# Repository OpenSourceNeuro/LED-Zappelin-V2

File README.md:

<h1 align="center"> LED Zappelin' v2</h1>
<h3 align="center">  An Open Source and versatile LED controller for arbitrary spectrum visual stimulation and optogenetics during two-photon imaging.</h3></p>
<h6 align="right">developed by M.J.Y. Zimmermann, A.M. Chagas & T. Baden</h6>

<br>

This project is licensed under the <a href="https://www.gnu.org/licenses/gpl-3.0.html">GNU General Public License v3.0</a>
<br>
The hardware is licensed under the <a href="https://cern-ohl.web.cern.ch">CERN OHL v1.2</a>

***

<p style='text-align: justify;'>
Two-photon microscopy is a cornerstone technique in neuroscience research, but combining this technology with spectrally arbitrary light stimulation can be challenging due to crosstalk between stimulation light and fluorescence detection. To overcome this limitation, we present LED Zappelin': a simple and low-cost electronic solution to rapidly time-interleave stimulation and detection epochs during scans.
</p>

The second version of this project allows user to either:

  - Independently drive up to 24 arbitrary spectrum LEDs to meet user requirements. Using the <a href="https://www.ti.com/lit/ds/symlink/tlc5947.pdf">TLC5947 LED driver</a>.
  - Control external light source generator such as the <a href="https://www.thorlabs.com/newgrouppage9.cfm?objectgroup_id=13597">Thorlabs Chrolis</a>. Using TTL logic circuits.

</br>

<h5 align="justify"> <em>Left: </em>LED Zappelin' mounted with a TLC 5947 controlling up to 24 LED channels. <em>Right: </em>LED Zappelin' mounted with TTL circuit controlling two 6-High_Power LED Chrolis systems</h5>

<br></br>

<p style='text-align: justify;'>
In the <a href=https://pubmed.ncbi.nlm.nih.gov/35498254/>original publication</a>, we demonstrate the utility of our stimulator for colour vision experiments on the in vivo tetra-chromatic zebrafish retina and for optogenetic circuit mapping in Drosophila.
</p>

<br>

- [Introduction](#Introduction)
- [BoM](https://github.com/BadenLab/LED-Zappelin/blob/master/Bills%20of%20Materials/BOM%20-%20Stimulator.csv)
- [Request a Quote]()
- [A stimulator for visual neuroscience](#Colour-Vision-Experiment)
- [A stimulator for optogenetics](#Optogenetics-Experiment)
- [A detailed assembly and instruction manual](https://github.com/BadenLab/LED-Zappelin/blob/master/Instruction%20Manual/README.md)
- [A step by step calibration script](https://github.com/BadenLab/LED-Zappelin/blob/master/Instruction%20Manual/Stimulator%20Calibration/Stimulator_Calibration.ipynb)
- [Repository Structure](#Repository-Structure)

<br>

## Introduction

<p align="justify">
Combining two-photon imaging with additional light stimulation – for example for visual stimulation or for driving optogenetic actuators – has remained challenging because the stimulation light can interfere with fluorescence detection. This can result in light artefacts in the image and/or may damage sensitive fluorescence detection equipment (e.g. photomultiplier tubes, PMTs).
</p>

<p align="justify">

A temporal separation between light stimulation and fluorescence detection, for example during the scan-retrace, can ameliorate these problems.
This problem can be readily solved electronically, for example through use of a microcontroller.
</p>

<br>

<p align="justify">
Here, we present such a solution. Our system can either line-synch up to 24 independent LED channels or can be connected to external commercial light sources, and can be assembled from off-the-shelf components for substantially below $200. This provides for flexible options of spectrally diverse light stimulation during two-photon scanning and comfortably provides sufficient power to drive standard optogenetics actuators such as CsChrimson.
</p>

<br>

<p align="justify">
Alongside, we also provided <a href="https://github.com/OpenSourceNeuro/LED-Zappelin-V2/tree/main/Casing%20Files">custom casing files</a> (for either 3d print or laser-cut), <a href="https://github.com/OpenSourceNeuro/LED-Zappelin-V2/tree/main/3D%20files">designed suggestions</a> for optically combining LED banks using Thorlabs parts, and an alternative 3D-printed LED holder and microscope chamber.
</p>

<p align="justify">
The device is built around an <a href="https://www.espressif.com/en/products/socs/esp32">ESP32</a>, a microcontroller which exchange signals with the recording setup, drive the light sources and runs on C++. However, users do not need to interfere with the source code as we provide an intuitive and interactive <a href="">Graphical User Interface</a> (GUI), from which all functions and variables can be manipulated.
</p>

</br>

<h5 align="justify"> <em>Left: </em>LED Zappelin' GUI controlling 4 LEDs, all executing a chirp stimulus. <em>Right: </em>LED Zappelin' controlling 12 LED channels from two Chrolis systems, executing successive On/Off stimulati</h5>

<br></br>

<p align="justify">
<a href="https://github.com/OpenSourceNeuro/LED-Zappelin-V2/blob/main/GUI_UserManual.md"><strong>Here</strong></a>, is the full user guide documentation.
</p>

<br>

***

## Colour Vision Experiment

<p align="justify">
We used LED Zappelin' for studying the retinal processing of the tetra-chromatic zebrafish retina in response to multichromatic signal.
Here we selected four LEDs that match the peak sensitivities of each cone opsins of our model.
We chose LEDs and band pass filters in such manner that the stimulating light and the detection bands do not overlap as much as possible. However a temporal separation is still necessary to avoid some overlapping and any light artefact.
</p>

</br>

<h5 align="justify"> <em>Left: </em>Zebrafish's opsin absorbance spectra overlapped with four filtered LED spectra. <em>Right: </em>The four selected stimulation LEDs along the microscope setup spectra features</h5>

<br></br>

<p align="justify">
 We recorded light-driven calcium signals under 2-photon from <a href="https://pubmed.ncbi.nlm.nih.gov/29937350/"> retinal bipolar cells in vivo in the tetra-chromatic larval zebrafish</a>. We used a transgenic line expressing a genetically encoded biosensors for calcium at the  bipolar cell synaptic terminals level (ctbp2:SyGCaMP6)  within the inner plexiform layer (IPL).
</p>

<p align="justify">
Following <a href="https://pubmed.ncbi.nlm.nih.gov/2321027/">established protocols</a>, we used a Sutter MOM microscope where light stimulation is displayed through the objective directly onto the fish retina along with the laser excitation. Fluorescence is also collected through the objective as well as from below the stage (not shown).
</p>

<p align="justify">
We presented full field steps of red, green, blue and UV light to the fish eye (respectively 567, 480, 420 and 365nm), and recorded evoked calcium signals as a readout of synaptic activity. We observed spectrally different tunings from distinct bipolar cell terminals  without detectable stimulus artefact across the scan.
</p>

<h5 align="justify"> a) Overview of the setup described for the visual stimulation experiment performed on the tetra-chromatic zebrafish. b) Drawing of the larval zebrafish retina highlighting the IPL. c) 2 photon scan field of the IPL with regions-of-interest marked by red circles. The 64x32 pixel image was obtained by at 1ms scan rate. d) Ca²⁺ traces (mean traces in black, n=5 trials in grey) in response to consecutive red, green, blue and UV On/Off flashes. e) Trigger timing recorded by the DAQ highlighting its accuracy over time with a precision of 0.1µs. t(n+1) = t(n) + T, where “t” is the recorded trigger time and “T” the trigger period. </5>

***

## Optogenetics Experiment

In addition to colour vision experiments, LED Zappelin' is well suited for optogenetic manipulations.

<p align="justify">
Here we illustrate this application in Drosophila larvae, were we recorded brain-wide calcium signals under 2P in response to optogenetic stimulation of all olfactory sensory neurons (OSNs).  We expressed the red-shifted channel rhodopsin CsChrimson OSNs and the genetically encoded calcium indicator GCaMP6s pan-neuronally by using larvae with the genotype: elav-Gal4;UAS-GCaMP6s/Orco-LexA;LexAOp-CsChrimson.
</p>

<p align="justify">
We placed first instar larvae under a custom-made 2P microscope in a <a href"https://github.com/OpenSourceNeuro/LED-Zappelin-V2/tree/main/3D%20files/Optogenetics%20Components">3D-printed optogenetics LED chamber</a>.
Red light stimulation was delivered from around the sides of the recording chamber and GCaMP6s fluorescence intensity was collected by two detectors one through the objective lens, and a sub-stage PMT.
We presented full field illumination steps of 615 nm light lasting 0.5 s and an inter-stimulus interval of either 3 s (b) or 10 s (c).
</p>

<p align="justify">
We observed robust stimulus-evoked activity in the primary olfactory sensory centres of the larval brain, the antennal lobes (red outlines). Similarly to colour vision experiments, we detected no light artefact.
</p>

<h5 align="justify">  a) Schematic of a fruit fly first instar larval head expressing the red-shifted channel rhodopsin CsChrimson in olfactory sensory neurons and GCaMP6s in all neurons. b) Rendering of the experimental setup: The mounting chamber is placed in a 3D-printed holder, screwed onto a rigid stand (ThorLabs).  c),d)  2 photon scan field of the larval brain with antennal lobes marked by red circles (left) and Ca²⁺ traces in response to red flashes (right). c. Stimulation duration = 0.5 s, inter-stimulus interval = 3 s, image dimensions = 256 x 230, scan rate = 1081 Hz, frame rate = 4.7 Hz. d) Stimulation duration = 0.5 s, inter-stimulus interval = 10 s, image dimensions = 256 x 170, scan rate = 1077Hz, frame rate = 6.34 Hz. </h5>

***
## Repository structure (to be updated)

```
├───3D Designs                                Contains printed parts for the stimulator and optical components
│   ├───Optical Components
|   |   ├───STL renderings                    - Printing files
|   |   └───SCAD files                        - SCAD files to be modified if need be
│   ├───Optogenetics Components
|   |   ├───STL renderings                    - Printing files
|   |   └───SCAD files                        - SCAD files to be modified if need be
│   └───Stimulator
|       ├───STL renderings                    - Printing files
|       └───SCAD files                        - SCAD files to be modified if need be
|
├───Arduino Code                              Stimulator Code
|   ├───Stimulator Code                       - Adaptable C+ code for running the stimulator
|   └───LED driver library                     - Library to run the TLC 5947
|
├───Bill of Materials                         List of necessary components and retailer suggestions
|
├───Datasheets                                - Contains all technical sheet for:
|   ├───Optical Components                    - ...LEDs, Filters, Dichroic Mirrors used in the presented example
|   ├───Stimulator                            - ...micro-controller and LED driver
|   └───Spectrometer                          - ...device used for calibration
|
├───Images                                    Image repository
|
├───Instruction Manual                        Detailed manual to assemble and calibrate the stimulator
|   └───Stimulator Calibration                - Contains calibration recordings and the adaptable jupyter notebook script to calibrate the stimulator
|       ├───Arduino Calibration Code          - Sequence used for the calibration
|       ├───Calibration Figures               - Illustration from calibration measurements
|       ├───Filters                           - Filters and dicroic mirrors spectra
|       ├───Powermeter Recording              - Recording of the calibration sequence
|       ├───Spectrometer Recording            - Recording of the calibration sequence
|       └───Stimulator Calibration            - iPython Jupyter Notebook script for calibration
|
├───PCB                                       KiCad and Gerber files to modified and generate PCB for:
│   ├───Potentiometer mounts                  - ...trimmer potentiometers that set the LED maximum brightness
│   └───Stimulator                            - ...the stimulator itself
|
└───References                                Publication used to design and conceive this model

```

***

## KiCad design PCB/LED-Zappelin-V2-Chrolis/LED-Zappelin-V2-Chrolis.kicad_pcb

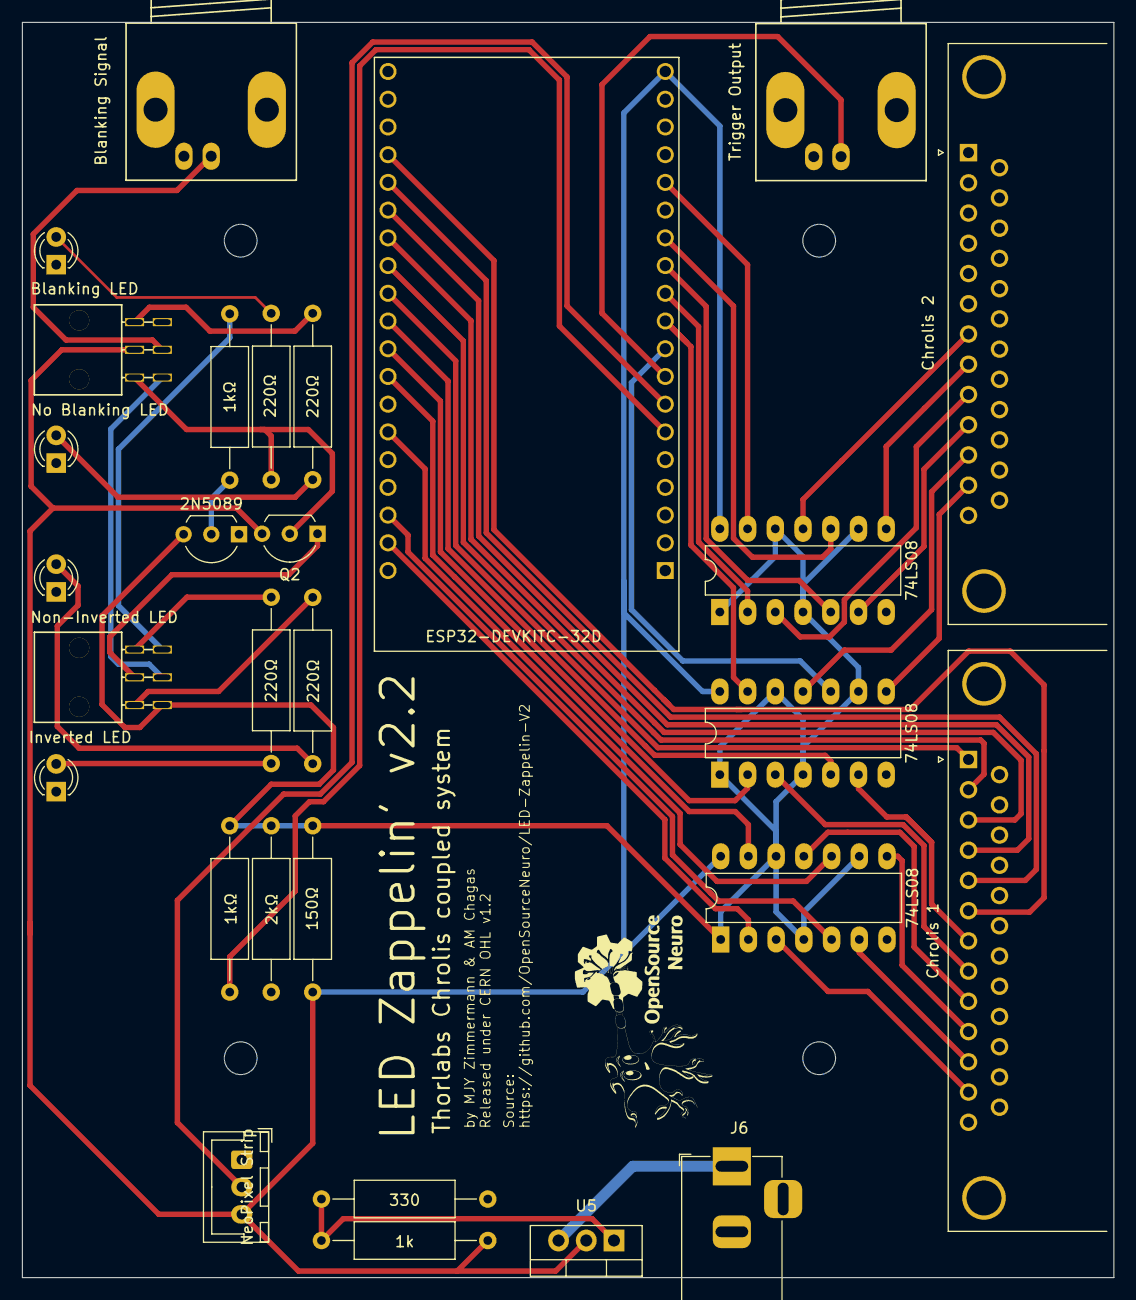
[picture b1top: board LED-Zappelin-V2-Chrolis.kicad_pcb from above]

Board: 2 copper layers, 100.0 x 115.0 mm, 33 parts (0 on the bottom side), 51 nets.

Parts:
D1: Blanking LED; LED_D3.0mm
D2: No Blanking LED; LED_D3.0mm
D3: Inverted LED; LED_D3.0mm
D4: Non-Inverted LED; LED_D3.0mm
H1, H2, H3, H4: MountingHole; MountingHole_3mm
J1: Blanking Signal; BNC_Socket_TYCO-AMP_LargePads
J2: Trigger Output; BNC_Socket_TYCO-AMP_LargePads
J3: Chrolis 1; DSUB-25_Female_Horizontal_P2.77x2.84mm_EdgePinOffset9.90mm_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
J4: Chrolis 2; DSUB-25_Female_Horizontal_P2.77x2.84mm_EdgePinOffset9.90mm_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
J5: NeoPixel Strip; JST_XH_B3B-XH-A_1x03_P2.50mm_Vertical
J6: Barrel_Jack; BarrelJack_Horizontal
Q1, Q2: 2N5089; TO-92L_Inline_Wide
R1, R6: 1kΩ; R_Axial_DIN0309_L9.0mm_D3.2mm_P15.24mm_Horizontal
R2: 2kΩ; R_Axial_DIN0309_L9.0mm_D3.2mm_P15.24mm_Horizontal
R3, R4, R7, R8: 220Ω; R_Axial_DIN0309_L9.0mm_D3.2mm_P15.24mm_Horizontal
R5: 150Ω; R_Axial_DIN0309_L9.0mm_D3.2mm_P15.24mm_Horizontal
R9: 1k; R_Axial_DIN0309_L9.0mm_D3.2mm_P15.24mm_Horizontal
R10: 330; R_Axial_DIN0309_L9.0mm_D3.2mm_P15.24mm_Horizontal
SW1: Blanking Switch; maxi_DPDT_Angled
SW2: Blanking Inverter Switch; maxi_DPDT_Angled
U1: ESP32-DEVKITC-32D; MODULE_ESP32-DEVKITC-32D
U2, U3, U4: 74LS08; DIP-14_W7.62mm_LongPads
U5: LM317_TO-220; TO-220-3_Vertical

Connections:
5V: J5.3, Q2.3 (C), R5.2, R9.2, SW1.5 (B), U1.19 (EXT_5V), U2.14 (VCC), U3.14 (VCC), U4.14 (VCC), U5.2 (VO)
+9V: J6.1, U5.3 (VI)
Blanking: Q1.3 (C), R1.2, R2.2, R5.1, SW2.3 (C), U2.1, U2.4, U2.9, U2.12, U3.1, U3.4, U3.9, U3.12, U4.1, U4.4, U4.9, U4.12
GNDREF: D1.1 (K), D2.1 (K), D3.1 (K), D4.1 (K), J1.2 (Ext), J2.2 (Ext), J3.13, J3.14, J3.15, J3.16, J3.17, J3.18, J3.19, J3.20, J3.21, J3.22, J3.23, J3.24, J3.25, J4.13, J4.14, J4.15, J4.16, J4.17, J4.18, J4.19, J4.20, J4.21, J4.22, J4.23, J4.24, J4.25, J5.1, J6.2, Q1.1 (E), R2.1, R10.1, U1.14 (GND1), U1.20 (GND3), U1.26 (GND2), U2.7 (GND), U3.7 (GND), U4.7 (GND)
GPIO00: J3.4, U1.33 (IO0)
GPIO02: J3.5, U1.34 (IO2)
GPIO04: J3.3, U1.32 (IO4)
GPIO05: U1.29 (IO5), U3.5
GPIO12: U1.13 (IO12), U4.10
GPIO13: U1.15 (IO13), U4.13
GPIO15: J3.6, U1.35 (IO15)
GPIO16: J3.2, U1.31 (IO16)
GPIO17: J3.1, U1.30 (IO17)
GPIO18: U1.28 (IO18), U3.2
GPIO19: U1.27 (IO19), U2.13
GPIO21: U1.25 (IO21), U2.10
GPIO22: U1.22 (IO22), U2.5
GPIO23: U1.21 (IO23), U2.2
GPIO25: U1.9 (IO25), U3.10
GPIO26: U1.10 (IO26), U3.13
GPIO27: U1.11 (IO27), U4.2
GPIO28: U1.12 (IO14), U4.5
GPIO Input 1: J3.12, U2.3
GPIO Input 2: J3.11, U2.6
GPIO Input 3: J3.10, U2.8
GPIO Input 4: J3.9, U2.11
GPIO Input 5: J3.8, U3.3
GPIO Input 6: J3.7, U3.6
GPIO Input 7: J4.12, U3.8
GPIO Input 8: J4.11, U3.11
GPIO Input 9: J4.10, U4.6
GPIO Input 10: J4.9, U4.3
GPIO Input 11: J4.8, U4.8
GPIO Input 12: J4.7, U4.11
NeoPixel: J5.2, U1.7 (IO32)
unnamed: D1.2 (A), R3.1
unnamed: D2.2 (A), R4.1
unnamed: D3.2 (A), R7.1
unnamed: D4.2 (A), R8.1
unnamed: J1.1 (In), SW1.2 (B)
unnamed: Q1.2 (B), R6.1
unnamed: Q2.2 (B), R3.2, SW1.6 (C)
unnamed: Q2.1 (E), SW2.5 (B)
unnamed: R4.2, SW1.4 (A)
unnamed: R6.2, SW2.1 (A)
unnamed: R7.2, SW2.4 (A)
unnamed: R8.2, SW2.6 (C)
unnamed: SW1.3 (C), SW2.2 (B)
unnamed: R1.1, U1.6 (IO35)
unnamed: R9.1, R10.2, U5.1 (ADJ)
Trigger: J2.1 (In), U1.8 (IO33)

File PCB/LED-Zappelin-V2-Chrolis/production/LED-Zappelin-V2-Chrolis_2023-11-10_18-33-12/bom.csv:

Designator,Footprint,Quantity,Value,LCSC Part #
D1,LED_D3.0mm,1,Blanking LED,
D2,LED_D3.0mm,1,No Blanking LED,
D3,LED_D3.0mm,1,Inverted LED,
D4,LED_D3.0mm,1,Non-Inverted LED,
"H1, H2, H3, H4",MountingHole_3mm,4,MountingHole,
J1,BNC_Socket_TYCO-AMP_LargePads,1,Blanking Signal,
J2,BNC_Socket_TYCO-AMP_LargePads,1,Trigger,
J3,DSUB-25_Female_Horizontal_P2.77x2.84mm_EdgePinOffset9.90mm_Housed_MountingHolesOffset11.32mm,1,Chrolis 1,
J4,DSUB-25_Female_Horizontal_P2.77x2.84mm_EdgePinOffset9.90mm_Housed_MountingHolesOffset11.32mm,1,Chrolis 2,
J5,JST_XH_B3B-XH-A_1x03_P2.50mm_Vertical,1,NeoPixel Strip,
J6,BarrelJack_Horizontal,1,Barrel_Jack,
"Q1, Q2",TO-92L_Inline_Wide,2,2N5089,
"R1, R6",R_Axial_DIN0309_L9.0mm_D3.2mm_P15.24mm_Horizontal,2,1kΩ,
R10,R_Axial_DIN0309_L9.0mm_D3.2mm_P15.24mm_Horizontal,1,330,
R2,R_Axial_DIN0309_L9.0mm_D3.2mm_P15.24mm_Horizontal,1,2kΩ,
"R3, R4, R7, R8",R_Axial_DIN0309_L9.0mm_D3.2mm_P15.24mm_Horizontal,4,220Ω,
R5,R_Axial_DIN0309_L9.0mm_D3.2mm_P15.24mm_Horizontal,1,150Ω,
R9,R_Axial_DIN0309_L9.0mm_D3.2mm_P15.24mm_Horizontal,1,1k,
SW1,maxi_DPDT_Angled,1,Blanking Switch,
SW2,maxi_DPDT_Angled,1,Blanking Inverter Switch,
U1,MODULE_ESP32-DEVKITC-32D,1,ESP32-DEVKITC-32D,
"U2, U3, U4",DIP-14_W7.62mm_LongPads,3,74LS08,
U5,TO-220-3_Vertical,1,LM317_TO-220,

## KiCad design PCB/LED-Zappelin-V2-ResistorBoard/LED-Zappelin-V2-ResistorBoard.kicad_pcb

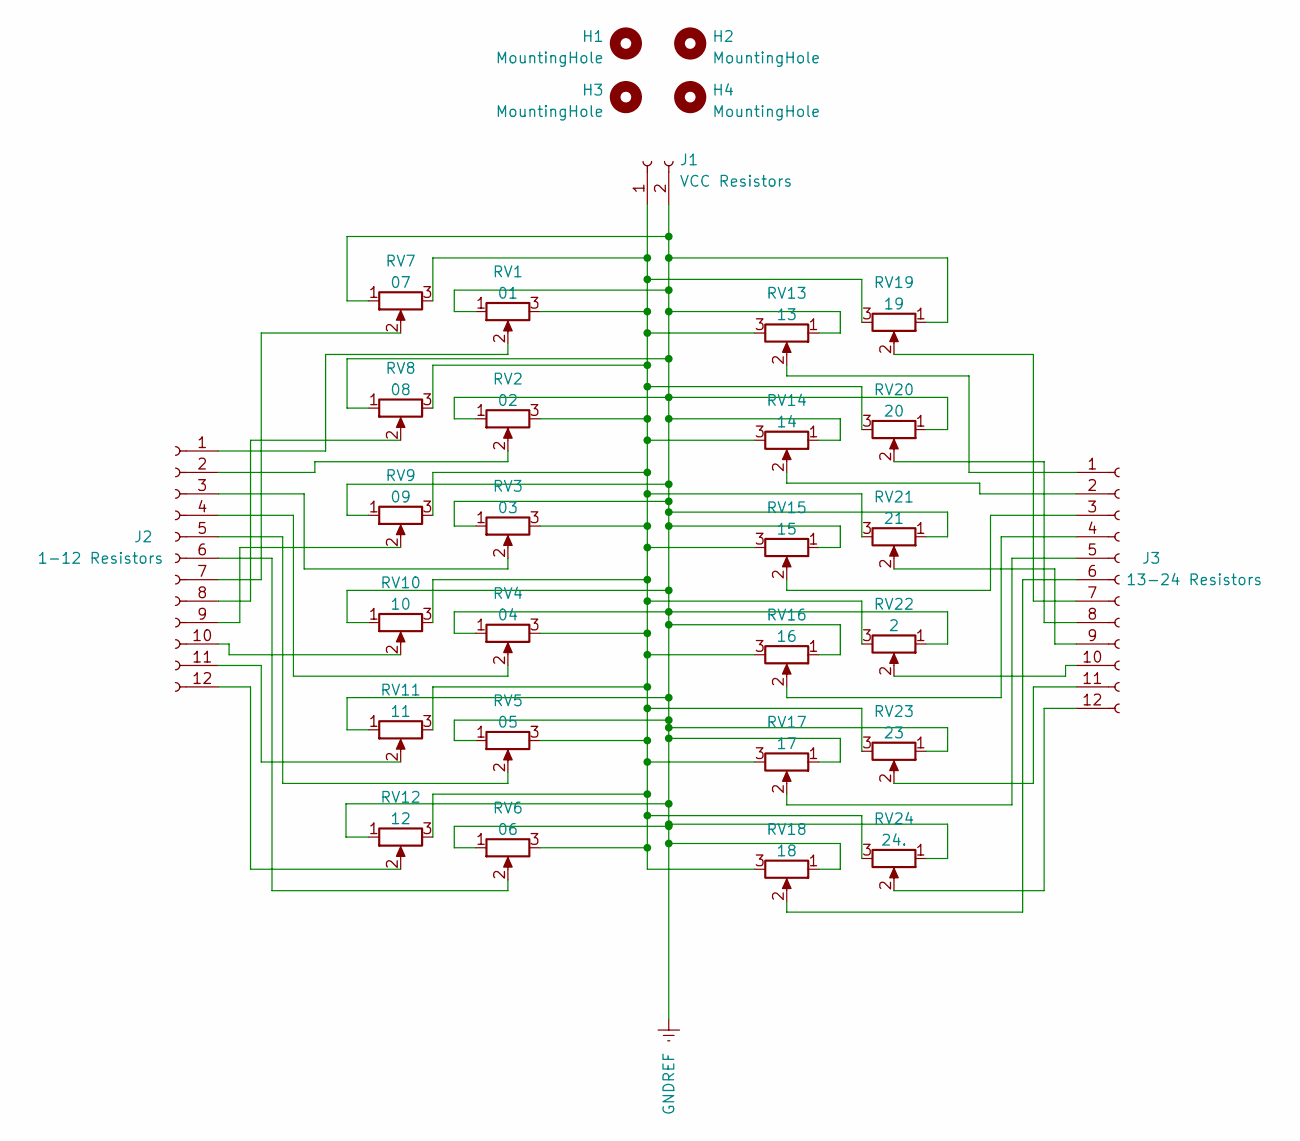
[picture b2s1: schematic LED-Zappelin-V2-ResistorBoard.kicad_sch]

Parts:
H1, H2, H3, H4: MountingHole; MountingHole_3mm
J1: VCC Resistors; JST_XH_S2B-XH-A-1_1x02_P2.50mm_Horizontal
J2: 1-12 Resistors; JST_XH_S12B-XH-A_1x12_P2.50mm_Horizontal
J3: 13-24 Resistors; JST_XH_S12B-XH-A_1x12_P2.50mm_Horizontal
RV1: 01; Potentiometer_Vishay_43_Horizontal
RV2: 02; Potentiometer_Vishay_43_Horizontal
RV3: 03; Potentiometer_Vishay_43_Horizontal
RV4: 04; Potentiometer_Vishay_43_Horizontal
RV5: 05; Potentiometer_Vishay_43_Horizontal
RV6: 06; Potentiometer_Vishay_43_Horizontal
RV7: 07; Potentiometer_Vishay_43_Horizontal
RV8: 08; Potentiometer_Vishay_43_Horizontal
RV9: 09; Potentiometer_Vishay_43_Horizontal
RV10: 10; Potentiometer_Vishay_43_Horizontal
RV11: 11; Potentiometer_Vishay_43_Horizontal
RV12: 12; Potentiometer_Vishay_43_Horizontal
RV13: 13; Potentiometer_Vishay_43_Horizontal
RV14: 14; Potentiometer_Vishay_43_Horizontal
RV15: 15; Potentiometer_Vishay_43_Horizontal
RV16: 16; Potentiometer_Vishay_43_Horizontal
RV17: 17; Potentiometer_Vishay_43_Horizontal
RV18: 18; Potentiometer_Vishay_43_Horizontal
RV19: 19; Potentiometer_Vishay_43_Horizontal
RV20: 20; Potentiometer_Vishay_43_Horizontal
RV21: 21; Potentiometer_Vishay_43_Horizontal
RV22: 2; Potentiometer_Vishay_43_Horizontal
RV23: 23; Potentiometer_Vishay_43_Horizontal
RV24: 24.; Potentiometer_Vishay_43_Horizontal

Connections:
GNDREF: J1.2, RV1.1, RV2.1, RV3.1, RV4.1, RV5.1, RV6.1, RV7.1, RV8.1, RV9.1, RV10.1, RV11.1, RV12.1, RV13.1, RV14.1, RV15.1, RV16.1, RV17.1, RV18.1, RV19.1, RV20.1, RV21.1, RV22.1, RV23.1, RV24.1
unnamed: J1.1, RV1.3, RV2.3, RV3.3, RV4.3, RV5.3, RV6.3, RV7.3, RV8.3, RV9.3, RV10.3, RV11.3, RV12.3, RV13.3, RV14.3, RV15.3, RV16.3, RV17.3, RV18.3, RV19.3, RV20.3, RV21.3, RV22.3, RV23.3, RV24.3
unnamed: J2.1, RV1.2
unnamed: J2.2, RV2.2
unnamed: J2.3, RV3.2
unnamed: J2.4, RV4.2
unnamed: J2.5, RV5.2
unnamed: J2.6, RV6.2
unnamed: J2.7, RV7.2
unnamed: J2.8, RV8.2
unnamed: J2.9, RV9.2
unnamed: J2.10, RV10.2
unnamed: J2.11, RV11.2
unnamed: J2.12, RV12.2
unnamed: J3.1, RV13.2
unnamed: J3.2, RV14.2
unnamed: J3.3, RV15.2
unnamed: J3.4, RV16.2
unnamed: J3.5, RV17.2
unnamed: J3.6, RV18.2
unnamed: J3.7, RV19.2
unnamed: J3.8, RV20.2
unnamed: J3.9, RV21.2
unnamed: J3.10, RV22.2
unnamed: J3.11, RV23.2
unnamed: J3.12, RV24.2

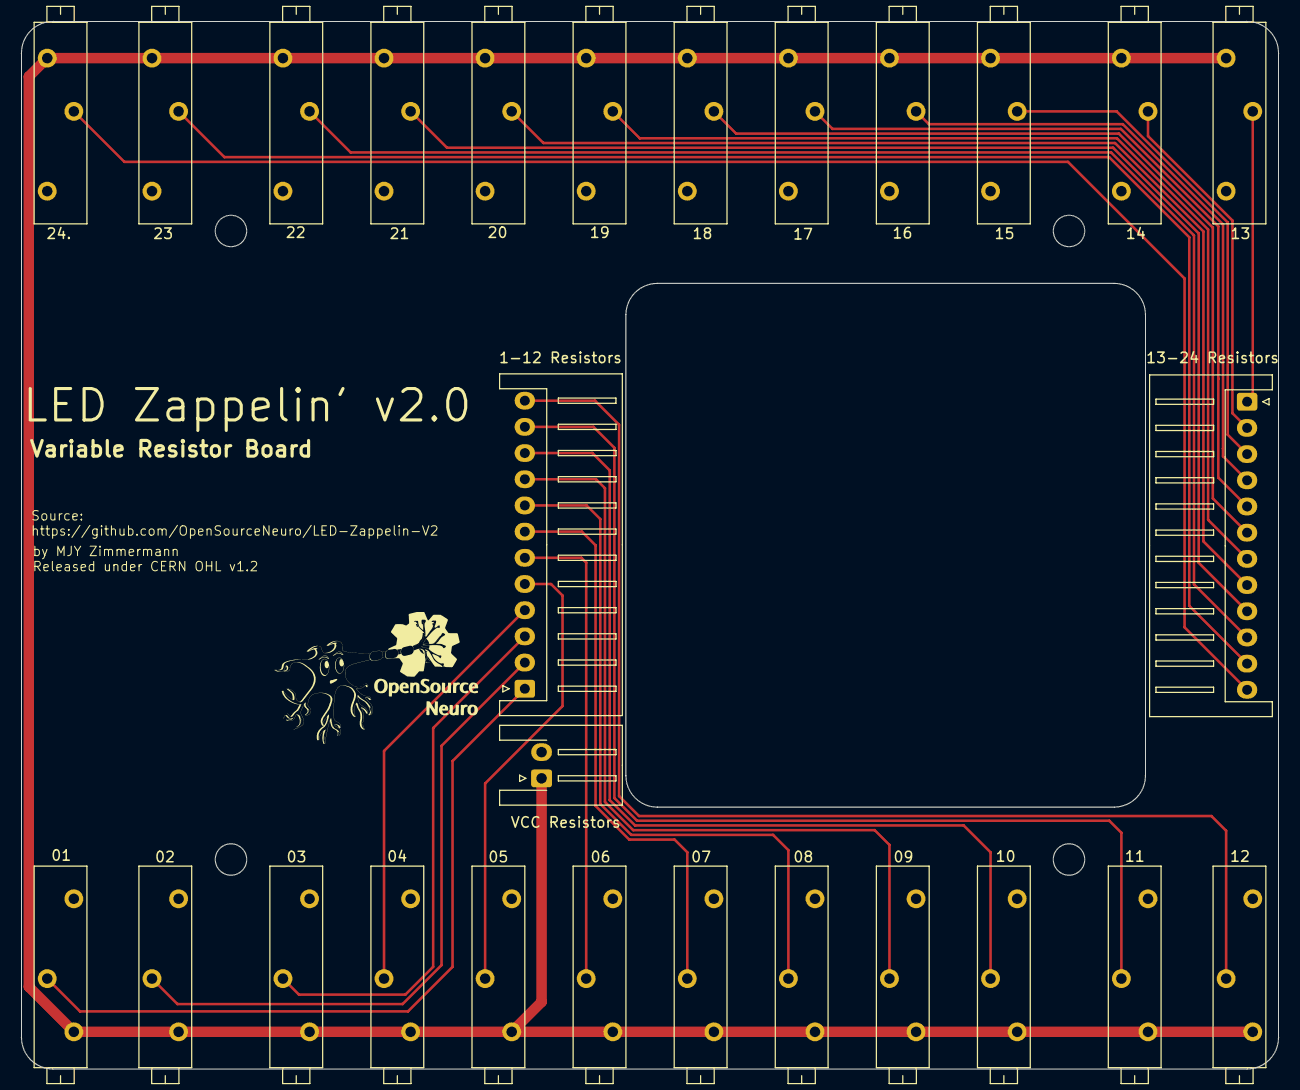
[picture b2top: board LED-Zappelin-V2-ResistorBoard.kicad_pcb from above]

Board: 2 copper layers, 120.0 x 100.0 mm, 31 parts (0 on the bottom side), 26 nets.

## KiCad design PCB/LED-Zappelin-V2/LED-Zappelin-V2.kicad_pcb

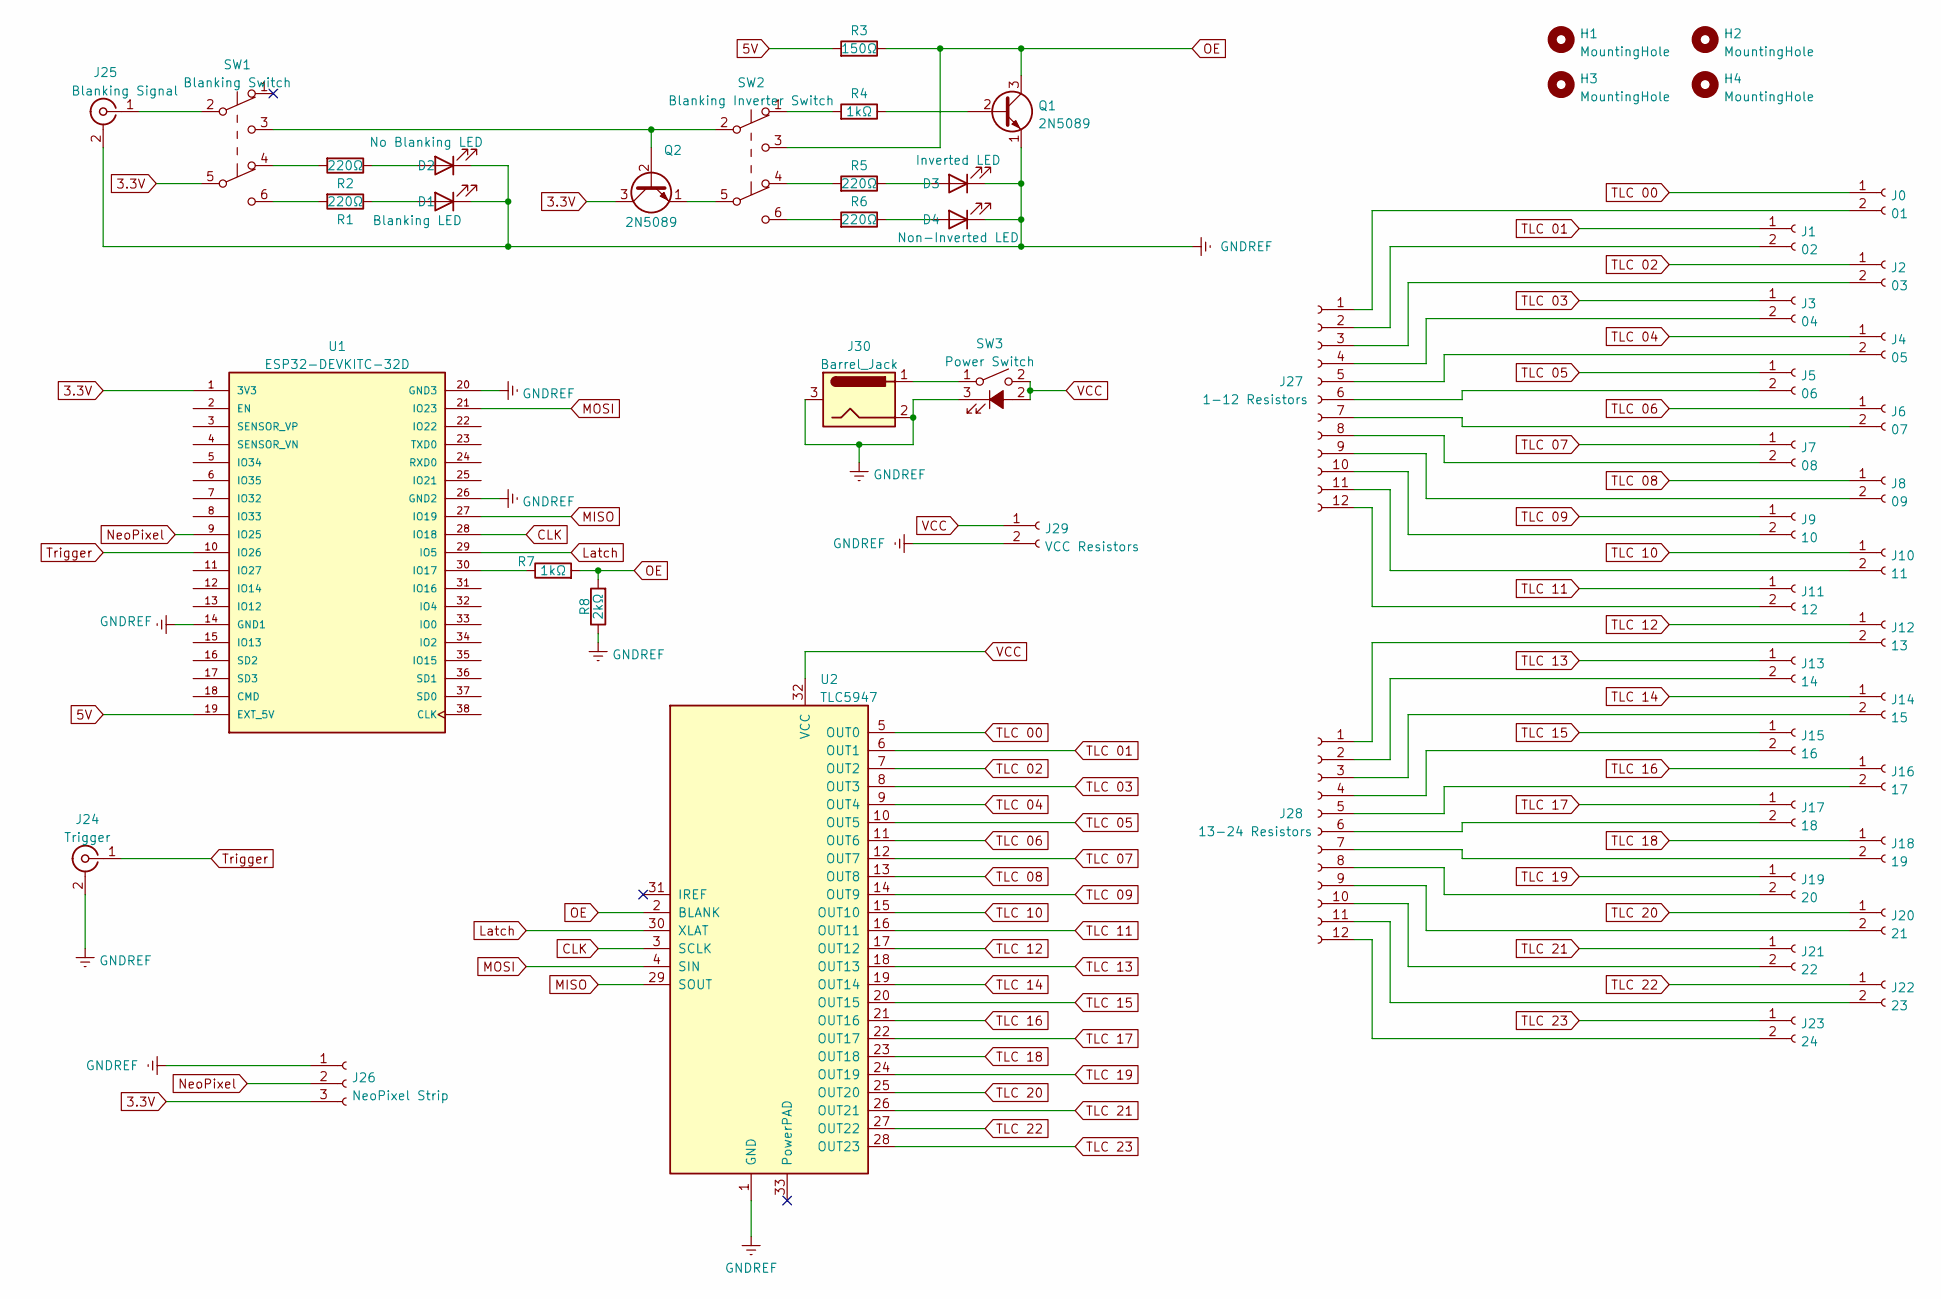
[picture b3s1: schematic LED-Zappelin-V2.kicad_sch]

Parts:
D1: Blanking LED; LED_D3.0mm
D2: No Blanking LED; LED_D3.0mm
D3: Inverted LED; LED_D3.0mm
D4: Non-Inverted LED; LED_D3.0mm
H1, H2, H3, H4: MountingHole; MountingHole_3mm
J0: 01; JST_XH_S2B-XH-A-1_1x02_P2.50mm_Horizontal
J1: 02; JST_XH_S2B-XH-A-1_1x02_P2.50mm_Horizontal
J2: 03; JST_XH_S2B-XH-A-1_1x02_P2.50mm_Horizontal
J3: 04; JST_XH_S2B-XH-A-1_1x02_P2.50mm_Horizontal
J4: 05; JST_XH_S2B-XH-A-1_1x02_P2.50mm_Horizontal
J5: 06; JST_XH_S2B-XH-A-1_1x02_P2.50mm_Horizontal
J6: 07; JST_XH_S2B-XH-A-1_1x02_P2.50mm_Horizontal
J7: 08; JST_XH_S2B-XH-A-1_1x02_P2.50mm_Horizontal
J8: 09; JST_XH_S2B-XH-A-1_1x02_P2.50mm_Horizontal
J9: 10; JST_XH_S2B-XH-A-1_1x02_P2.50mm_Horizontal
J10: 11; JST_XH_S2B-XH-A-1_1x02_P2.50mm_Horizontal
J11: 12; JST_XH_S2B-XH-A-1_1x02_P2.50mm_Horizontal
J12: 13; JST_XH_S2B-XH-A-1_1x02_P2.50mm_Horizontal
J13: 14; JST_XH_S2B-XH-A-1_1x02_P2.50mm_Horizontal
J14: 15; JST_XH_S2B-XH-A-1_1x02_P2.50mm_Horizontal
J15: 16; JST_XH_S2B-XH-A-1_1x02_P2.50mm_Horizontal
J16: 17; JST_XH_S2B-XH-A-1_1x02_P2.50mm_Horizontal
J17: 18; JST_XH_S2B-XH-A-1_1x02_P2.50mm_Horizontal
J18: 19; JST_XH_S2B-XH-A-1_1x02_P2.50mm_Horizontal
J19: 20; JST_XH_S2B-XH-A-1_1x02_P2.50mm_Horizontal
J20: 21; JST_XH_S2B-XH-A-1_1x02_P2.50mm_Horizontal
J21: 22; JST_XH_S2B-XH-A-1_1x02_P2.50mm_Horizontal
J22: 23; JST_XH_S2B-XH-A-1_1x02_P2.50mm_Horizontal
J23: 24; JST_XH_S2B-XH-A-1_1x02_P2.50mm_Horizontal
J24: Trigger; BNC_Socket_TYCO-AMP_LargePads
J25: Blanking Signal; BNC_Socket_TYCO-AMP_LargePads
J26: NeoPixel Strip; JST_XH_B3B-XH-A_1x03_P2.50mm_Vertical
J27: 1-12 Resistors; JST_XH_B12B-XH-A_1x12_P2.50mm_Vertical
J28: 13-24 Resistors; JST_XH_B12B-XH-A_1x12_P2.50mm_Vertical
J29: VCC Resistors; JST_XH_B2B-XH-A_1x02_P2.50mm_Vertical
J30: Barrel_Jack; BarrelJack_Horizontal
Q1, Q2: 2N5089; TO-92L_Inline_Wide
R1, R2, R5, R6: 220Ω; R_Axial_DIN0309_L9.0mm_D3.2mm_P15.24mm_Horizontal
R3: 150Ω; R_Axial_DIN0309_L9.0mm_D3.2mm_P15.24mm_Horizontal
R4, R7: 1kΩ; R_Axial_DIN0309_L9.0mm_D3.2mm_P15.24mm_Horizontal
R8: 2kΩ; R_Axial_DIN0309_L9.0mm_D3.2mm_P15.24mm_Horizontal
SW1: Blanking Switch; maxi_DPDT_Angled
SW2: Blanking Inverter Switch; maxi_DPDT_Angled
SW3: Power Switch; JST_XH_B3B-XH-A_1x03_P2.50mm_Vertical
U1: ESP32-DEVKITC-32D; MODULE_ESP32-DEVKITC-32D; PARTREV 4
U2: TLC5947; Maxi_TLC5947

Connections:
3.3V: J26.3, Q2.3 (C), SW1.5 (B), U1.1 (3V3)
5V: R3.2, U1.19 (EXT_5V)
CLK: U1.28 (IO18), U2.3 (SCLK)
GNDREF: D1.1 (K), D2.1 (K), D3.1 (K), D4.1 (K), J24.2 (Ext), J25.2 (Ext), J26.1, J29.2, J30.2, J30.3, Q1.1 (E), R8.1, SW3.3 (K), U1.14 (GND1), U1.20 (GND3), U1.26 (GND2), U2.1 (GND)
Latch: U1.29 (IO5), U2.30 (XLAT)
MISO: U1.27 (IO19), U2.29 (SOUT)
MOSI: U1.21 (IO23), U2.4 (SIN)
NeoPixel: J26.2, U1.9 (IO25)
unnamed: D1.2 (A), R1.1
unnamed: D2.2 (A), R2.1
unnamed: D3.2 (A), R5.1
unnamed: D4.2 (A), R6.1
unnamed: J0.2, J27.1
unnamed: J1.2, J27.2
unnamed: J2.2, J27.3
unnamed: J10.2, J27.11
unnamed: J11.2, J27.12
unnamed: J12.2, J28.1
unnamed: J13.2, J28.2
unnamed: J14.2, J28.3
unnamed: J15.2, J28.4
unnamed: J16.2, J28.5
unnamed: J17.2, J28.6
unnamed: J18.2, J28.7
unnamed: J19.2, J28.8
unnamed: J20.2, J28.9
unnamed: J21.2, J28.10
unnamed: J22.2, J28.11
unnamed: J23.2, J28.12
unnamed: J3.2, J27.4
unnamed: J4.2, J27.5
unnamed: J5.2, J27.6
unnamed: J6.2, J27.7
unnamed: J7.2, J27.8
unnamed: J8.2, J27.9
unnamed: J9.2, J27.10
unnamed: J30.1, SW3.1
unnamed: Q1.2 (B), R4.1
unnamed: Q2.1 (E), SW2.5 (B)
unnamed: Q2.2 (B), SW1.3 (C), SW2.2 (B)
unnamed: R4.2, SW2.1 (A)
unnamed: R5.2, SW2.4 (A)
unnamed: R6.2, SW2.6 (C)
unnamed: R7.1, U1.30 (IO17)
unnamed: J25.1 (In), SW1.2 (B)
unnamed: R2.2, SW1.4 (A)
unnamed: R1.2, SW1.6 (C)
OE: Q1.3 (C), R3.1, R7.2, R8.2, SW2.3 (C), U2.2 (BLANK)
TLC 00: J0.1, U2.5 (OUT0)
TLC 01: J1.1, U2.6 (OUT1)
TLC 02: J2.1, U2.7 (OUT2)
TLC 03: J3.1, U2.8 (OUT3)
TLC 04: J4.1, U2.9 (OUT4)
TLC 05: J5.1, U2.10 (OUT5)
TLC 06: J6.1, U2.11 (OUT6)
TLC 07: J7.1, U2.12 (OUT7)
TLC 08: J8.1, U2.13 (OUT8)
TLC 09: J9.1, U2.14 (OUT9)
TLC 10: J10.1, U2.15 (OUT10)
TLC 11: J11.1, U2.16 (OUT11)
TLC 12: J12.1, U2.17 (OUT12)
TLC 13: J13.1, U2.18 (OUT13)
TLC 14: J14.1, U2.19 (OUT14)
TLC 15: J15.1, U2.20 (OUT15)
TLC 16: J16.1, U2.21 (OUT16)
TLC 17: J17.1, U2.22 (OUT17)
TLC 18: J18.1, U2.23 (OUT18)
TLC 19: J19.1, U2.24 (OUT19)
TLC 20: J20.1, U2.25 (OUT20)
TLC 21: J21.1, U2.26 (OUT21)
TLC 22: J22.1, U2.27 (OUT22)
TLC 23: J23.1, U2.28 (OUT23)
Trigger: J24.1 (In), U1.10 (IO26)
VCC: J29.1, SW3.2, U2.32 (VCC)

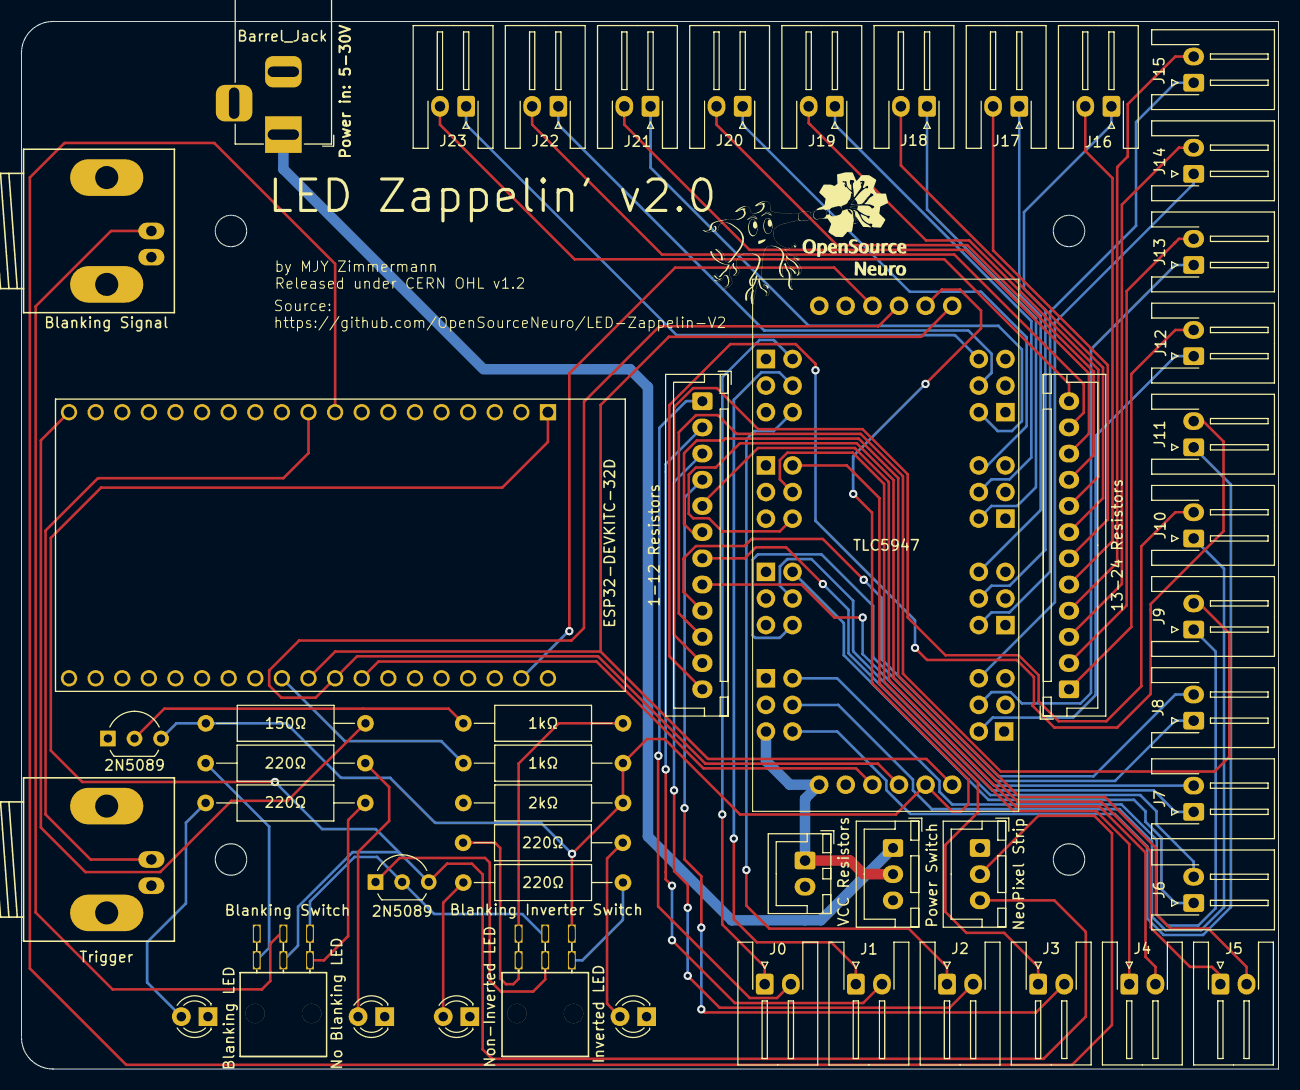
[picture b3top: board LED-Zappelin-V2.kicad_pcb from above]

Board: 2 copper layers, 120.0 x 100.0 mm, 54 parts (0 on the bottom side), 74 nets.

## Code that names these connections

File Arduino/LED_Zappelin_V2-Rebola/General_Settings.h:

/*          ---  General Settings  ---
*/
#include "LED_Values.h"                     // Include LED Values defined in the second tab
#include <SPI.h>                            // Include the arduino serial port interface library
#include "Adafruit_TLC5947.h"               // Include the Adafruit TLC5947 libvrary. For better result one may change the number of channel defined in the Adafruit_TLC5947.cpp library
#include <Adafruit_NeoPixel.h>


#define   MISO           23                 // TLC SPI connection, Data Out
#define   MOSI           19                 // TLC SPI connection, Data In 
#define   CLK            18                 // TLC SPI connection, Clock 
#define   latch          5                  // TLC Latch
#define   Blank          17                 // TLC Ouput Enable, Also Optional feature to prevent LED to light up when powering up the TLC board

#define   NeoPixel       25                 // NeoPixel pin
#define   NeoPixel_LED   16                 // Number of NeoPixel LEDs

#define   Trigger        26                 // Trigger channel 


    Adafruit_TLC5947 tlc = Adafruit_TLC5947(1, CLK, MISO, latch);
    //Adafruit_NeoPixel strip(NeoPixel_LED, NeoPixel, NEO_GRB + NEO_RGBW);
    Adafruit_NeoPixel strip(NeoPixel_LED, NeoPixel, NEO_GRB + NEO_KHZ800);


/* ----------------------------------------------------------------------------------*/
/* ------------------------------- Global Variables ---------------------------------*/

word           BaudRate      = 921600;      // Baud Rate speed
char           sCmd;                        // Serial monitor 
float          aNumber;
char           *arg;

bool           StimulusFlag = false;
bool           flag;
int            i;                           // Iteration loop factor
int            iLoop;
int            CurrentMicros;               // Current Microsecond clock
int            PreviousMicros;              // Microsecond clock stamp
int            DiffMicros;                  // Difference in microseconds between the clock and the stamp
int            ResolutionMicros;            // Microseconds delay between two i iteration
int            PreAdaptMicros;              // Preadaptation period in microseconds
bool           PreAdaptationFlag;

bool           TriggerState;

int            brightness    = 100;         // NeoPixel brightness (max = 255)
int            l;                           // LED iteration factor


/* ----------------------------------------------------------------------------------*/
/* --------------------- LED Zappelion' initialising conditions ---------------------*/
void HardwareSettings(){
  
// Initialise the serial communication with PC
  Serial.begin(BaudRate);                      
  
// Initialise the Adafruit TLC driver 
  tlc.begin();
  tlc.write();  

// Initialise the Neopixel Strip
  if (OldNeopixel == true){
    Adafruit_NeoPixel strip(NeoPixel_LED, NeoPixel, NEO_GRB + NEO_KHZ800);
  }
  strip.begin();           
  strip.show();                    // Turn OFF all pixels ASAP
  strip.setBrightness(brightness); // Set NeoPixel brightness 

// Set pins
  pinMode(Trigger, INPUT);   
  pinMode(Blank, INPUT);
  digitalWrite(Blank, HIGH);
  pinMode(13,OUTPUT);


// Initialise parameters
  l = 0;
  CurrentMicros = 0;
  PreviousMicros = 0;
  DiffMicros = 0;
  flag = true;
  TriggerState = LOW;
}

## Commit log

2023-07-26 First commit - 3D
2023-07-26 First commit - Arduino
2023-07-26 First commit - PCB
2023-07-26 First commit - GUI
2023-08-16 Update Casing files
2023-08-16 Create 3D files
2023-08-16 add LED_Zappelin.exe
2023-08-25 Update Notebooks
2023-08-25 update Notebook
2023-08-25 Update Stimuli
2023-08-25 Update Arduino
2023-08-25 update GUI
2023-10-10 update Arduinos
2023-11-01 update Arduino libraries
2023-11-01 update Images
2023-11-07 update PCB
2023-11-07 Update Manuals
2023-11-09 Update 3D files
2023-11-09 update.exe
2023-11-10 update board for chrolis
    This update adds a voltage regulator to the board, as well as a connection to an external power supply. Footprints have been moved around so that only two sides of the board have connectors.
2023-11-11 update PCB
    Previous modifications were kept, transistor Q2 was rerouted to sw1 pin6, all power line are now linked to external 5v power supply.
    PCB was rearranged to accommodate box equipment. The neopixel strip for example requires 110mm +some tolerance on one side
2024-01-22 upload direct trigger verion
2024-01-23 update direct trigger
2024-01-23 Update XinWei version
2024-01-23 Chrolis default arduino
2024-01-23 upload Attach-Interrupt version
2024-03-05 update £d files

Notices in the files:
PCB/LED-Zappelin-V2-Chrolis/LED-Zappelin-V2-Chrolis.kicad_pcb:
Released under CERN OHL v1.2
